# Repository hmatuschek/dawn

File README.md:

# Bluetooth controlled dawn simulator

This is a simple Bluetooth controlled bedside light which can act as a dawn simulator.

**Disclaimer**: The hardware schematics provided here deal with relatively high currents 
(depending on the LED used, >1A) which may even cause fire. If you rebuild the hardware,
you do that on our own risk! I am not responsible for any damage caused by the circuits 
or the software provided here. In general, do not rebuild the hardware if you do not 
understand the circuit completely!

## Hardware

The hardware ([schematics](https://github.com/hmatuschek/dawn/blob/master/doc/lampe_brd.pdf) 
can be found in the hardware/ directory) consists of a high-power LED, a current regulator
(BUZ11 + 2x BC547),  an ATMega168 MCU, a real-time clock (DS1307) with back-up battery
and a RS232 Bluetooth interface module (JY-MCU).

The [circuit](https://github.com/hmatuschek/dawn/blob/master/doc/lampe_brd.pdf) can be 
adopted easily to different LEDs by changing the value of R25 and/or R30 such that 
R25||R30 = 0.6/Imax, where Imax is the maximum current through the LED. Please be aware 
that the MOSFET Q4 as well as the LED may need some cooling.

The brightness of the LED will be controlled by the PWM output (pin 15) of the ATMega.

The firmware for the ATMega168 can be found in the firmware/ directory.

## Software

The software can be found in the src/ directory and provides a simple GUI using QT5 to configure and
control the dawn simulator. 

The dawn simulator is interfaced via Bluetooth, hence you must first connect to the device using the 
OS Bluetooth configuration. This will create a new serial port (RS232) which needs to be selected 
within the GUI application. 

## Communication protocol

The communication protocol is a trivial binary one. Every command/request is transmitted in terms of 
messages. The basic message structure is

    +--------+-- ... --+-- ... --+
    |  CMD   | PAYLOAD |   MAC   |
    +--------+---... --+-- ... --+

Each command message consists of a 8-bit command field, an optional Payload (variable size)
and a message authentication code (64 bit).

The RS232 Bluetooth module has only a 4-digit PIN for the access control. Hence some
additional measures are needed. Every message send to the device is therefore authenticated
using a simple MAC. The MAC is computed over the CMD and PAYLOAD fields of the message 
using the SIPHASH(2,4) function with a shared secret. This does not provide a very high 
level of security but may be considered sufficient for a bedside light.

Please note that the device will not send any response on an error. I.e. if an invalid command is received 
or if the MAC is invalid.

### (H)MAC algorithm

The signature (64bit) is simply the SipHash-2-4 of the message body with a shared 128bit secret.

  MAC = siphash24(MESSAGE, SECRET)

Please note that there is no IV that changes with every command. Hence the protocol is in principle 
vulnerable to replay attacks. Although the Bluetooth authentication is secured using a trivial 
4-digit PIN, the actual communication is encrypted with a relatively strong algorithm and key. 
Unless an attacker is able to capture the pairing, the communication should be relatively robust 
against trivial replay attacks. 

### GET_VALUE command (0x01)

Returns the current luminescence value of the lamp. This command has no payload.

The response contains the current value as a uint16_t as the payload.

### SET_VALUE command (0x02)

Sets the current luminescence value of the lamp.

The command payload contains the value as a uint16_t.

On success, a single byte (0x00) is returned.

### GET_TIME command (0x03)

Returns the current date and time of the RTC.

The command has no payload.

The response payload has the following structure

YEAR:MONTH:DAY:DAYOFWEEK:HOUR:MINTUE:SECOND

Where YEAR is transmitted as a uint16_t and MONTH, DAY, DAYOFWEEK, HOUR, MINUTE and SECOND as
uint8_t.

### SET_TIME command (0x04)

Set the current date and time of the RTC.

The command payload has the following structure

YEAR:MONTH:DAY:DAYOFWEEK:HOUR:MINTUE:SECOND

Where YEAR is transmitted as a uint16_t and MONTH, DAY, DAYOFWEEK, HOUR, MINUTE and SECOND as
uint8_t.

On success, a single byte (0x00) is returned.

### GET_ALARM command (0x05)

Returns the settings for the i-th alarm, where i in [0,6]

The payload contains the index of the alarm as a uint8_t.

The response Payload has the following format

DOW_FLAGS:HOUR:MINUTE

The first bit (MSB) is reserved (0), followed by 7 bits encoding the day of the week at which 
the alarm is enabled. 

0b0000001 - Sunday
0b0000010 - Monday
0b0000100 - Tuesday
0b0001000 - Wednesday
0b0010000 - Thursday
0b0100000 - Friday
0b1000000 - Saturday

Hence a value of 0x7f will enable the alarm on every day and a value of 0x00 will effectively disable
the alarm.

HOUR and MINUTE are encoded as uint8_t.

### SET_ALARM command (0x06)

Sets the i-th alarm settings, where i in [0,6].

The command payload has the following format:

IDX:DOW_FLAGS:HOUR:MINUTE

Where IDX is encodes the alarm index as uint8_t. The 7 least significant bits of DOW_FLAGS encode 
the day of the week at which the alarm is enabled.

0b0000001 - Sunday
0b0000010 - Monday
0b0000100 - Tuesday
0b0001000 - Wednesday
0b0010000 - Thursday
0b0100000 - Friday
0b1000000 - Saturday

HOUR and MINUTE are encoded as uint8_t.

### GET_TEMP command (0x07)

Returns the core and ambient temperature in K.

The response has the following format

CORE_TEMP:AMB_TEMP

where both variables are 16bit integer values (MSB first). Some MCUs do not
provide a core temperature sensor. In this case 0xffff is returned.

## License

dawn - A dawn-simulating bedside light.

Copyright (C) 2015  Hannes Matuschek

This program and harware is "free software"; you can redistribute it 
and/or modify it under the terms of the GNU General Public License
as published by the Free Software Foundation; either version 2 of 
the License, or (at your option) any later version.

This program and hardware is distributed in the hope that it will be useful,
but WITHOUT ANY WARRANTY; without even the implied warranty of
MERCHANTABILITY or FITNESS FOR A PARTICULAR PURPOSE.  See the
GNU General Public License for more details.

You should have received a copy of the GNU General Public License along
with this program; if not, write to the Free Software Foundation, Inc.,
51 Franklin Street, Fifth Floor, Boston, MA 02110-1301 USA.

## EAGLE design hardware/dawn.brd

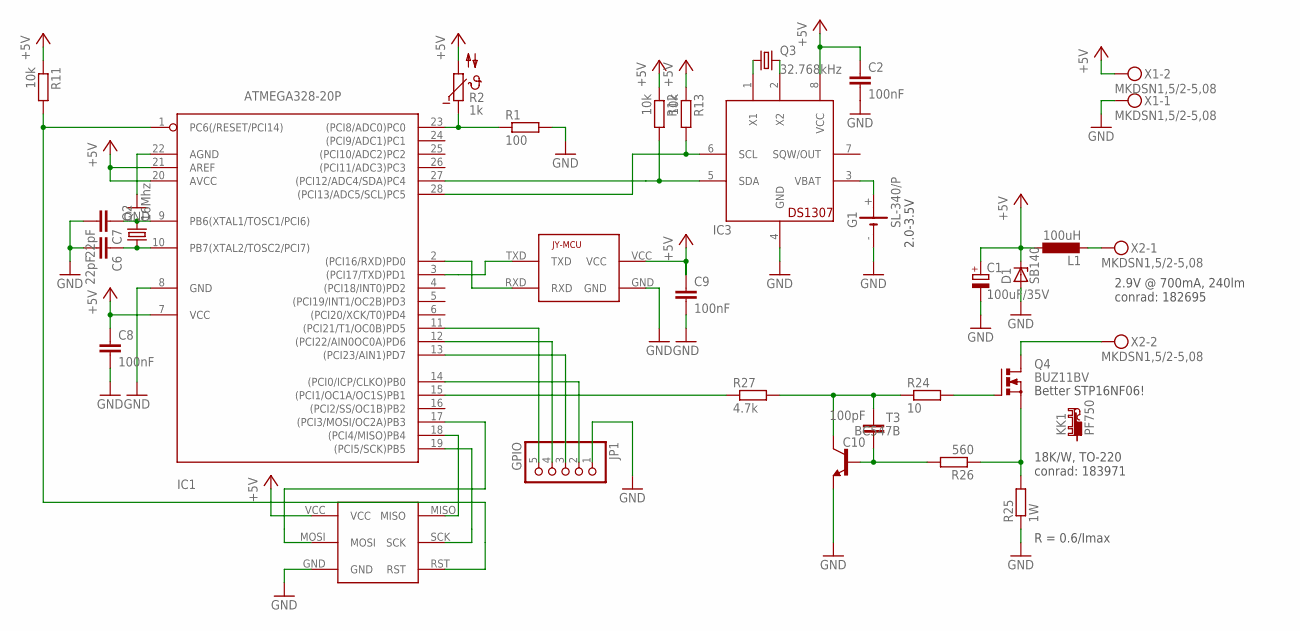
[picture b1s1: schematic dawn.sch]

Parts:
C1: 100uF/35V; E5-6
C2, C8, C9: 100nF; C025-025X050
C6: 22pF; C050-025X075
C7: 22pF; C025-025X050
C10: 100pF; C025-025X050
D1: SB140; DO35Z10
G1: SL-340/P; BEL/P
IC1: ATMEGA328-20P; DIL28-3
IC3: DS1307; DIL08
JP1: GPIO; 1X05
KK1: PF750; PF752
L1: 100uH; 6000-XXXX-RC
Q2: 16Mhz; HC18U-V
Q3: 32.768kHz; TC26V
Q4: BUZ11BV; TO220BV
R1: 100; 0204V
R2: 1k; B57164
R11: 10k; 0207/10
R12: 10k; 0204/5
R13: 10k; 0204V
R24: 10; 0204/7
R25: 1W; 0411/12
R26: 560; 0207/17
R27: 4.7k; 0207/10
T3: BC547B; TO92-EBC
U$1: JY-MCU
U$2: AVR-ISP
X1, X2: MKDSN1,5/2-5,08

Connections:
+5V: C1.+, C2.1, C8.1, C9.1, D1.C, IC1.7 (VCC), IC1.20 (AVCC), IC1.21 (AREF), IC3.8 (VCC), L1.1, R2.2, R11.1, R12.1, R13.1, U$1.VCC, U$2.VCC, X1.2
GND: C1.-, C2.2, C6.2, C7.2, C8.2, C9.2, D1.A, G1.-, IC1.8 (GND), IC1.22 (AGND), IC3.4 (GND), JP1.1, R1.2, R25.1, T3.E, U$1.GND, U$2.GND, X1.1
unnamed: IC1.15 ((PCI1/OC1A/OC1S)PB1), R27.1
unnamed: IC1.18 ((PCI4/MISO)PB4), U$2.MISO
unnamed: IC1.19 ((PCI5/SCK)PB5), U$2.SCK
unnamed: IC1.1 (PC6(/RESET/PCI14)), R11.2, U$2.RST
unnamed: IC1.17 ((PCI3/MOSI/OC2A)PB3), U$2.MOSI
unnamed: IC1.12 ((PCI22/AIN0OC0A)PD6), JP1.4
unnamed: IC1.11 ((PCI21/T1/OC0B)PD5), JP1.5
unnamed: IC1.13 ((PCI23/AIN1)PD7), JP1.3
unnamed: IC1.14 ((PCI0/ICP/CLKO)PB0), JP1.2
unnamed: IC1.23 ((PCI8/ADC0)PC0), R1.1, R2.1
unnamed: L1.2, X2.1
unnamed: C7.1, IC1.9 (PB6(XTAL1/TOSC1/PCI6)), Q2.2
unnamed: IC3.2 (X2), Q3.2
unnamed: IC3.1 (X1), Q3.1
unnamed: Q4.D, X2.2
unnamed: C6.1, IC1.10 (PB7(XTAL2/TOSC2/PCI7)), Q2.1
unnamed: IC1.28 ((PCI13/ADC5/SCL)PC5), IC3.6 (SCL), R13.2
unnamed: IC1.27 ((PCI12/ADC4/SDA)PC4), IC3.5 (SDA), R12.2
unnamed: G1.+, IC3.3 (VBAT)
unnamed: IC1.3 ((PCI17/TXD)PD1), U$1.TXD
unnamed: IC1.2 ((PCI16/RXD)PD0), U$1.RXD
unnamed: Q4.G, R24.2
unnamed: Q4.S, R25.2, R26.1
unnamed: C10.1, R26.2, T3.B
unnamed: C10.2, R24.1, R27.2, T3.C

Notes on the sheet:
2.9V @ 700mA, 240lm conrad: 182695
18K/W, TO-220 conrad: 183971
2.0-3.5V
R = 0.6/Imax
Better STP16NF06!

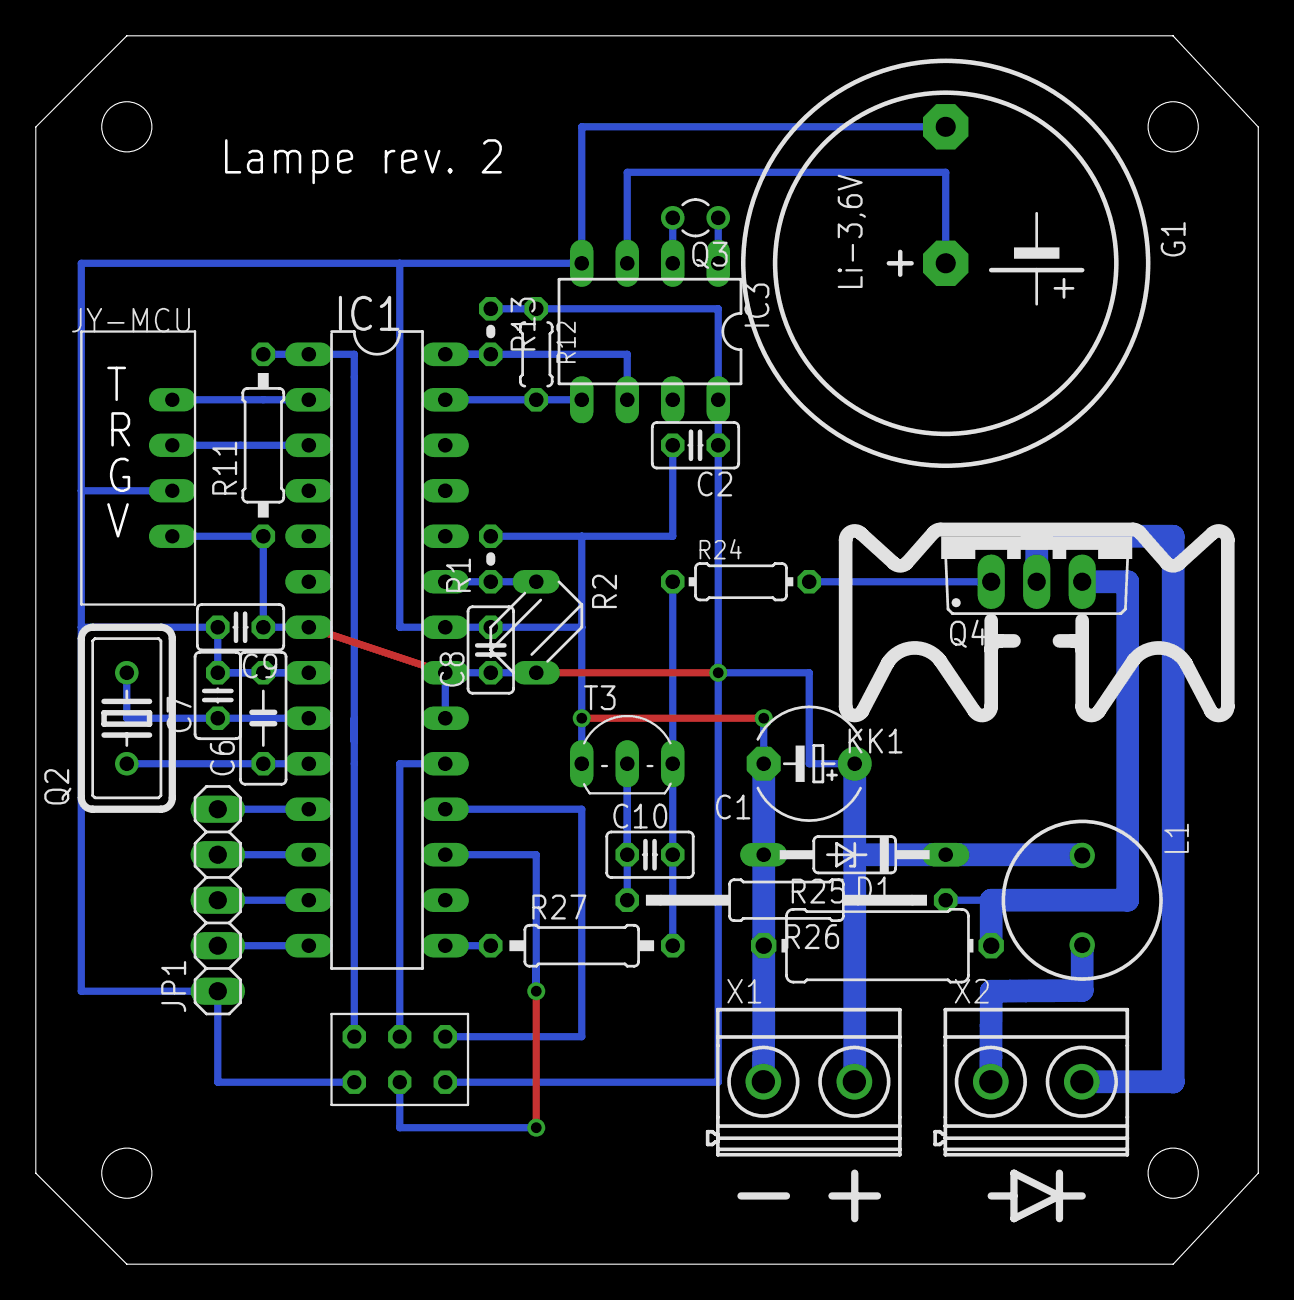
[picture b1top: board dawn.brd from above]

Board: 2 copper layers, 68.2 x 68.6 mm, 31 parts (0 on the bottom side), 27 nets.

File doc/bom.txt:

Qty Value           Device             Package         Parts    Description                          
1   10              R-EU_0204/7        0204/7          R24      RESISTOR
1   560             R-EU_0207/17       0207/17         R26      RESISTOR, European symbol            
2   1k              R-EU_0204/2V       0204V           R1, R28  RESISTOR
1   4.7k            R-EU_0207/10       0207/10         R27      RESISTOR, European symbol            
4   10k             R-EU_0204/2V       0204V           R13, R29, R12, R11 RESISTOR
1   1W              R-EU_0411/12       0411/12         R25      RESISTOR
1   10k             B57164             B57164          R2       SIEMENS NTC                          

2   22pF            C-EU025-025X050    C025-025X050    C7,C6    CAPACITOR
2   100nF           C-EU025-025X050    C025-025X050    C8, C9   CAPACITOR, European symbol           
1   100pF           C-EU025-025X050    C025-025X050    C10      CAPACITOR, European symbol           
1   100uF/35V       CPOL-EUE5-6        E5-6            C1       POLARIZED CAPACITOR

1   100uH           L-EU6000-XXX-RC    6000-XXXX-RC    L1       INDUCTOR, European symbol            

1   32.768kHz       CRYSTALTC26V       TC26V           Q3       CRYSTAL                              
1   16Mhz           CRYSTALHC18U-V     HC18U-V         Q2       CRYSTAL                              

1   ATMEGA328-20P   ATMEGA328-20P      DIL28-3         IC1      MICROCONTROLLER                      
1   JY-MCU          JY-MCU             JY-MCU          U$1      BLUETOOTH MODULE                                     

1   SB140           ZENER-DIODEDO35Z10 DO35Z10         D1       Z-Diode                              
2   BC547B          -NPN-TO92-EBC      TO92-EBC        T3, T4   NPN Transistror                      
1   BUZ11BV         BUZ11BV            TO220BV         Q4       N-CHANNEL MOS FET                    
1   DS1307          DS1307             DIL08           IC3      DS1307                               

2   MKDSN1,5/2-5,08 MKDSN1,5/2-5,08    MKDSN1,5/2-5,08 X1, X2   MKDSN 1,5/ 2-5,08 Printklemme        
1   PF750           PF750              PF752           KK1      HEATSINK                             
1   SL-340/P        SL-340/P           BEL/P           G1       LI BATTERY Sonnenschein

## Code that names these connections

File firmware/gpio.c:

#include "gpio.h"
#include <avr/io.h>

// PIN0 -> PB0
// PIN1 -> PD7
// PIN2 -> PD6
// PIN3 -> PD5

#define KEY_HOLD_DUR  100

typedef struct {
  KeyState last_state;
  KeyState state;
  uint16_t tick_count;
} KeyContext;

static KeyContext keys[3] = {
  {KEY_NONE, KEY_NONE, 0},
  {KEY_NONE, KEY_NONE, 0},
  {KEY_NONE, KEY_NONE, 0}
};

void
key_init() {
  // PD7, PD6, PD5 are inputs
  DDRD  &= ~((1 << DDD7) | (1 << DDD6) | (1 << DDD5));
  // Enables pull-ups
  PORTD |= ((1 << DDD7) | (1 << DDD6) | (1 << DDD5));
  // Init keys
  keys[0].last_state = keys[0].state = KEY_NONE;  keys[0].tick_count = 0;
  keys[1].last_state = keys[1].state = KEY_NONE;  keys[1].tick_count = 0;
  keys[2].last_state = keys[2].state = KEY_NONE;  keys[2].tick_count = 0;
}


void key_update(uint8_t key) {
  // Get current output values:
  uint8_t k   = 1;
  switch (key) {
  case 0: k = (PIND & (1<<DDD7)); break;
  case 1: k = (PIND & (1<<DDD6)); break;
  case 2: k = (PIND & (1<<DDD5)); break;
  }
  if (0 == k) {
    switch (keys[key].last_state) {
    case KEY_NONE:
      keys[key].last_state = KEY_CLICK;
      keys[key].tick_count = 0;
      break;
    case KEY_CLICK:
      if (keys[key].tick_count == 5) {
        keys[key].last_state = KEY_HOLD;
        keys[key].state      = KEY_HOLD;
      } else {
        keys[key].tick_count++;
      }
      break;
    case KEY_HOLD:
      break;
    }
  } else {
    switch (keys[key].last_state) {
    case KEY_NONE:
      keys[key].state = KEY_NONE;
      break;
    case KEY_CLICK:
      keys[key].last_state = KEY_NONE;
      keys[key].state      = KEY_CLICK;
      break;
    case KEY_HOLD:
      keys[key].last_state = KEY_NONE;
      keys[key].state      = KEY_NONE;
      break;
    }
    keys[key].tick_count = 0;
  }
}


KeyState key(uint8_t key) {
  return keys[key].state;
}

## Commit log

2014-11-22 Initial import.
2014-11-22 Cleanup
2014-11-22 Added main window.
2014-11-22 Minors
2014-11-22 Fixed commands.
2014-11-22 Fixed minors in firmware.
2014-11-23 Added config dialog.
2014-11-23 Fixed schematic & board.
2014-11-29 Fixed serial communication.
2015-01-14 Implemented CBC-MAC using siphash-2-4.
2015-06-16 Fixed.
2015-06-17 Minors.
2015-06-17 Added missing file.
2015-06-17 Fixed current reg.
2015-06-17 Updated circuit and board PDFs.
2015-06-18 Fixed build scripts for compilation under linux.
2015-06-18 Cleanup.
2015-06-18 Updated schematics and firmware for ATMEGA328P.
2015-07-24 Added logger.
2015-07-24 Fixed log messages.
2015-07-27 Fixed touch sensor code.
2015-07-27 Fixed stupid error in keygen.
2016-01-03 Fixed minors.
2016-01-13 Fixed memory corruption.
2016-01-16 Fixed MacOS icons.
2016-01-16 Added build-script option.
2016-01-16 Added windows build scripts.
2016-01-16 Fixed config.
2016-01-16 oops.
2016-01-16 Fixed minor.
2016-01-16 Fixed build.
2016-01-16 Fixed win build.
2016-05-22 Started command line tool.
2016-05-22 Added some output.
2016-05-22 Added info text.
2016-05-22 Added on/off ...
2016-09-23 Added debug messages.
2017-01-14 Test.
2017-01-14 backup.
2017-01-15 Minor.
2017-01-15 Fixed debug.
2017-01-15 Fixed interface.
2017-01-15 Extended cmd line interface.
2017-01-15 Backup
2017-01-16 Fixed commandline interface.
2017-01-16 Fixed cmd line.
2017-01-16 Fixed UART interface.
2017-01-16 Extended cmd.
2017-01-16 Added FCGI server.
2017-01-16 Fixed content-type.
2017-01-16 Fixed connection init.
2017-01-16 Added signal handler.
2017-01-16 Ext. JSON app. server.
2017-01-16 Extended JSON interface.
2017-01-17 Fixed JSON server.
2017-01-17 Fixed web interface.
